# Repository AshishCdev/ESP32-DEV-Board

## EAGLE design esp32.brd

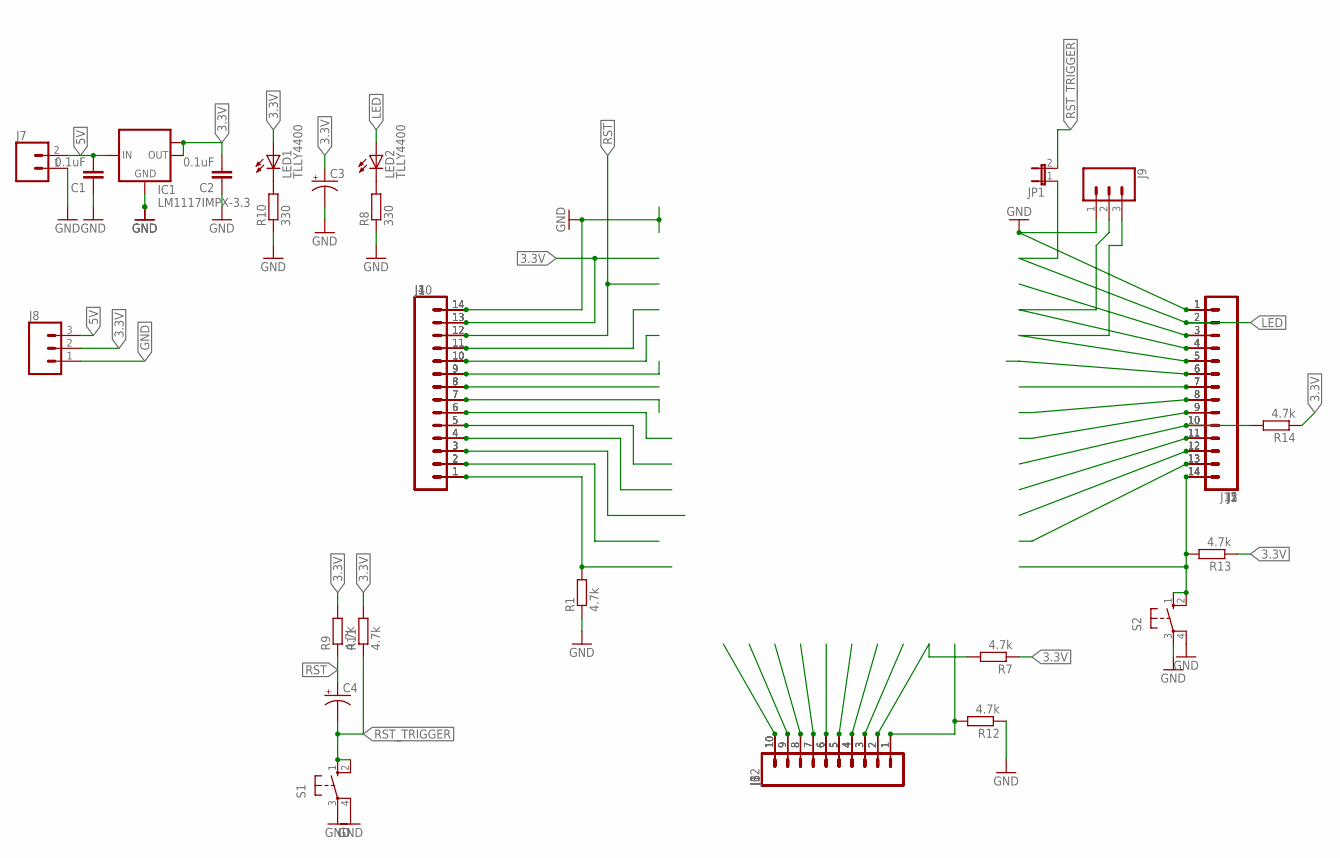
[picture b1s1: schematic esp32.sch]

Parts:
C1, C2: 0.1uF; CAP-PTH-SMALL-KIT
C3, C4: CPOL-USE3.5-8; E3,5-8
IC1: LM1117IMPX-3.3; SOT223
J1, J2, J4, J5, J10, J11: CONN_14LONGPADS; 1X14-LONGPADS
J3, J6, J12: CONN_10"; 1X10
J7: CONN_023.5MM; SCREWTERMINAL-3.5MM-2
J8, J9: CONN_03; 1X03
JP1: JP1E; JP1
LED1, LED2: TLLY4400; LED3MM
R1, R7, R9, R11, R12, R13, R14: 4.7k; 0207/12
R8, R10: 330; 0207/12
S1, S2: 10-XX; B3F-10XX

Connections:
3.3V: C2.2, C3.+, IC1.2 (OUT), IC1.TAB (OUT1), J1.13, J4.13, J8.2, J10.13, LED1.A, R7.1, R9.2, R11.2, R13.1, R14.1
5V: C1.2, IC1.3 (IN), J7.2, J8.3
GND: C1.1, C2.1, C3.-, IC1.1 (GND), J1.14, J2.1, J3.10, J4.14, J5.1, J6.10, J7.1, J8.1, J9.1, J10.14, J11.1, J12.10, R1.1, R8.1, R10.1, R12.1, S1.3, S1.4 (P1), S2.3, S2.4 (P1)
LED: J2.2, J5.2, J11.2, JP1.1, LED2.A
unnamed: J2.7, J5.7, J11.7
unnamed: J1.11, J4.11, J10.11
unnamed: J1.10, J4.10, J10.10
unnamed: LED1.K (C), R10.2
unnamed: LED2.K (C), R8.2
unnamed: J1.9, J4.9, J10.9
unnamed: J1.8, J4.8, J10.8
unnamed: J1.7, J4.7, J10.7
unnamed: J1.6, J4.6, J10.6
unnamed: J1.5, J4.5, J10.5
unnamed: J1.4, J4.4, J10.4
unnamed: J1.3, J4.3, J10.3
unnamed: J1.2, J4.2, J10.2
unnamed: J1.1, J4.1, J10.1, R1.2
unnamed: J2.5, J5.5, J9.3, J11.5
unnamed: J2.4, J5.4, J9.2, J11.4
unnamed: J2.3, J5.3, J11.3
unnamed: J2.10, J5.10, J11.10, R14.2
unnamed: J2.6, J5.6, J11.6
unnamed: J2.8, J5.8, J11.8
unnamed: J2.9, J5.9, J11.9
unnamed: J2.11, J5.11, J11.11
unnamed: J2.12, J5.12, J11.12
unnamed: J2.13, J5.13, J11.13
unnamed: J2.14, J5.14, J11.14, R13.2, S2.1 (S), S2.2 (S1)
unnamed: J3.9, J6.9, J12.9
unnamed: J3.8, J6.8, J12.8
unnamed: J3.7, J6.7, J12.7
unnamed: J3.6, J6.6, J12.6
unnamed: J3.5, J6.5, J12.5
unnamed: J3.4, J6.4, J12.4
unnamed: J3.3, J6.3, J12.3
unnamed: J3.2, J6.2, J12.2, R7.2
unnamed: J3.1, J6.1, J12.1, R12.2
RST: C4.+, J1.12, J4.12, J10.12, R9.1
RST_TRIGGER: C4.-, JP1.2, R11.1, S1.1 (S), S1.2 (S1)

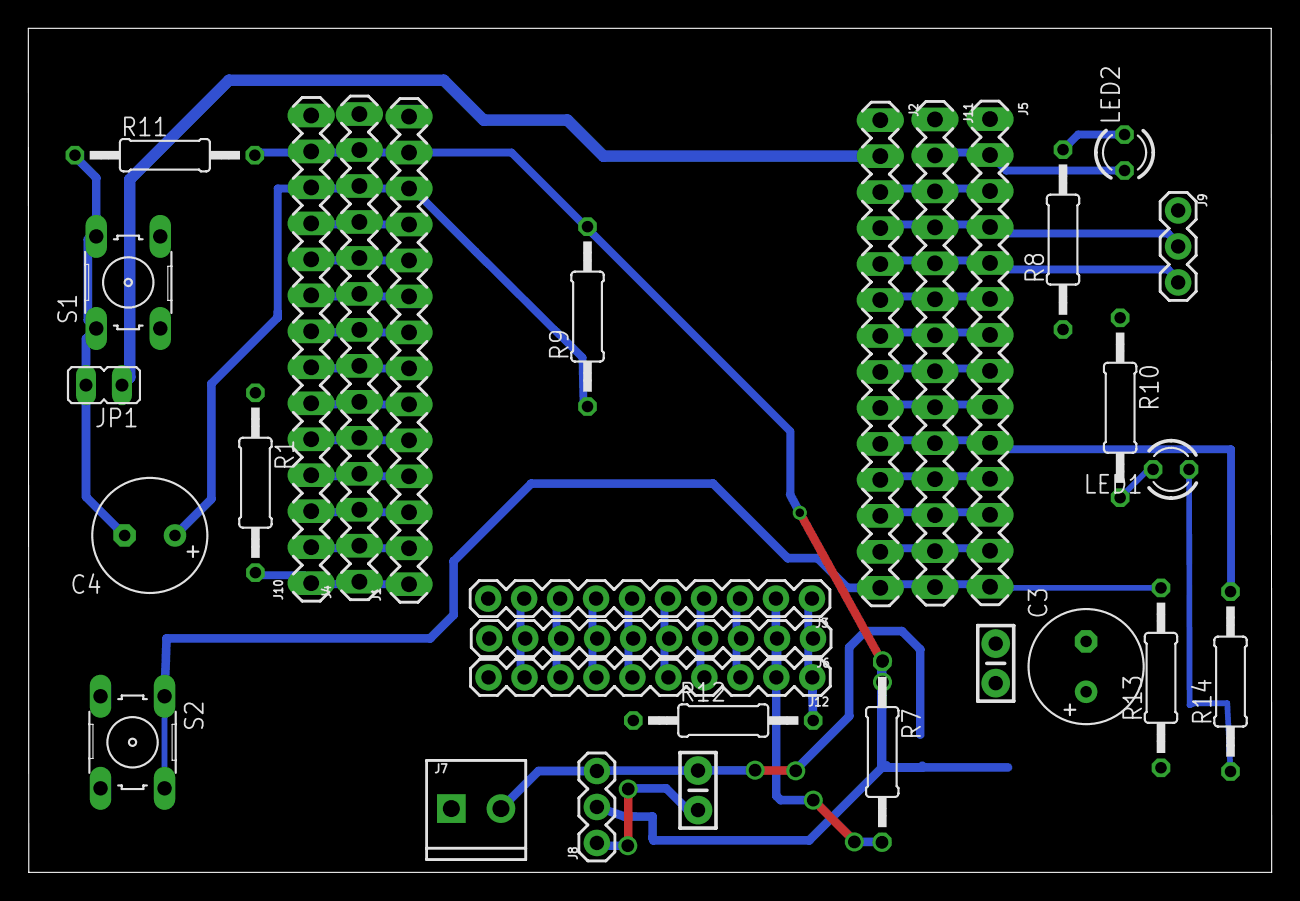
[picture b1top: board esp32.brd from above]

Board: 2 copper layers, 87.8 x 59.6 mm, 31 parts (1 on the bottom side), 40 nets.

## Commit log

2017-05-23 Inherited the project from breakout board
2017-05-23 connected dual line headers
2017-05-23 Reconstructed the schematic due to eagle error
2017-05-24 Added the reset circuitry
2017-05-24 Added all the GPIO strapping bias resistors
2017-05-24 Added LEDs and improved reset circuitry
2017-05-24 Finalized the layout with cheap design

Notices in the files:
parts and their libraries:
SparkFun-Connectors: Licensing: Creative Commons ShareAlike 4.0 International - https://creativecommons.org/licenses/by-sa/4.0
